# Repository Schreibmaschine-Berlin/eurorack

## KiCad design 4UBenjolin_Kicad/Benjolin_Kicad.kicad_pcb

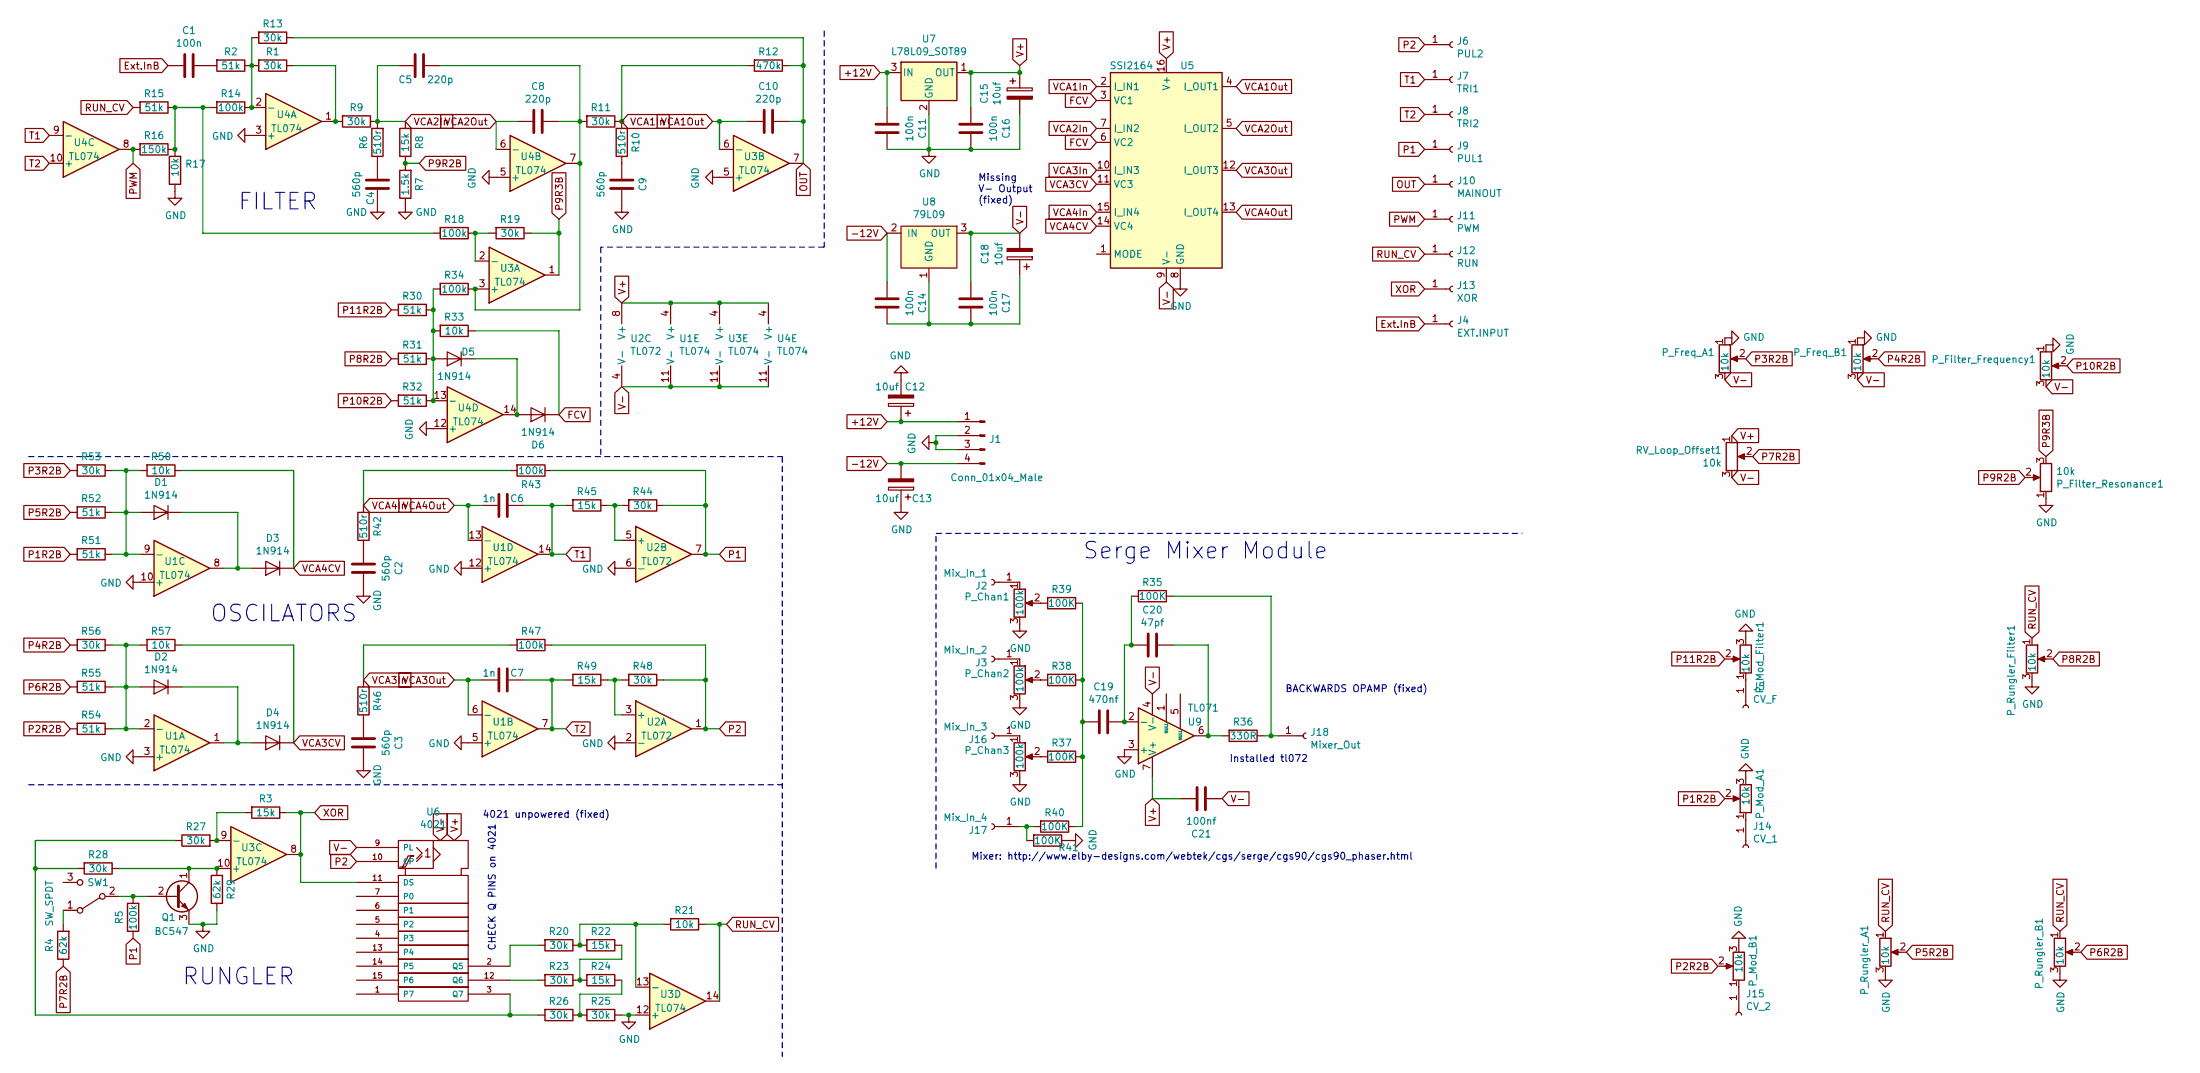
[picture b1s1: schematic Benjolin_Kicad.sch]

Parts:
C1, C11, C14, C16, C17: 100n; C_Disc_D8.0mm_W2.5mm_P5.00mm
C2, C3, C4, C9: 560p; C_Disc_D8.0mm_W2.5mm_P5.00mm
C5, C8, C10: 220p; C_Disc_D8.0mm_W2.5mm_P5.00mm
C6, C7: 1n; C_Disc_D8.0mm_W2.5mm_P5.00mm
C12, C13, C15, C18: 10uf; CP_Radial_D5.0mm_P2.50mm
C19: 470nf; C_Disc_D8.0mm_W2.5mm_P5.00mm
C20: 47pf; C_Disc_D8.0mm_W2.5mm_P5.00mm
C21: 100nf; C_Disc_D8.0mm_W2.5mm_P5.00mm
D1, D2, D3, D4, D5, D6: 1N914; D_A-405_P7.62mm_Horizontal
J1: Conn_01x04_Male; PinHeader_1x04_P2.54mm_Vertical
J2: Mix_In_1; Banana_Jack_PCB
J3: Mix_In_2; Banana_Jack_PCB
J4: EXT.INPUT; Banana_Jack_PCB
J5: CV_F; Banana_Jack_PCB
J6: PUL2; Banana_Jack_PCB
J7: TRI1; Banana_Jack_PCB
J8: TRI2; Banana_Jack_PCB
J9: PUL1; Banana_Jack_PCB
J10: MAINOUT; Banana_Jack_PCB
J11: PWM; Banana_Jack_PCB
J12: RUN; Banana_Jack_PCB
J13: XOR; Banana_Jack_PCB
J14: CV_1; Banana_Jack_PCB
J15: CV_2; Banana_Jack_PCB
J16: Mix_In_3; Banana_Jack_PCB
J17: Mix_In_4; Banana_Jack_PCB
J18: Mixer_Out; Banana_Jack_PCB
P_Chan1, P_Chan2, P_Chan3: 100k; Potentiometer_Alps_RK09K_Single_Vertical
P_Filter_Frequency1: 10k; Potentiometer_Alps_RK09K_Single_Vertical
P_Filter_Resonance1: 10k; Potentiometer_Alps_RK09K_Single_Vertical
P_Freq_A1: 10k; Potentiometer_Alps_RK09K_Single_Vertical
P_Freq_B1: 10k; Potentiometer_Alps_RK09K_Single_Vertical
P_Mod_A1: 10k; Potentiometer_Alps_RK09K_Single_Vertical
P_Mod_B1: 10k; Potentiometer_Alps_RK09K_Single_Vertical
P_Mod_Filter1: 10k; Potentiometer_Alps_RK09K_Single_Vertical
P_Rungler_A1: 10k; Potentiometer_Alps_RK09K_Single_Vertical
P_Rungler_B1: 10k; Potentiometer_Alps_RK09K_Single_Vertical
P_Rungler_Filter1: 10k; Potentiometer_Alps_RK09K_Single_Vertical
Q1: BC547; TO-92_Inline
R1, R9, R11, R13, R19, R20, R23, R25, R26, R27, R28, R44, R48, R53, R56: 30k; R_Axial_DIN0204_L3.6mm_D1.6mm_P7.62mm_Horizontal
R2, R15, R30, R31, R32, R51, R52, R54, R55: 51k; R_Axial_DIN0204_L3.6mm_D1.6mm_P7.62mm_Horizontal
R3, R8, R22, R24, R45, R49: 15k; R_Axial_DIN0204_L3.6mm_D1.6mm_P7.62mm_Horizontal
R4, R29: 62k; R_Axial_DIN0204_L3.6mm_D1.6mm_P7.62mm_Horizontal
R5, R14, R18, R34, R43, R47: 100k; R_Axial_DIN0204_L3.6mm_D1.6mm_P7.62mm_Horizontal
R6, R10, R42, R46: 510r; R_Axial_DIN0204_L3.6mm_D1.6mm_P7.62mm_Horizontal
R7: 1.5k; R_Axial_DIN0204_L3.6mm_D1.6mm_P7.62mm_Horizontal
R12: 470k; R_Axial_DIN0204_L3.6mm_D1.6mm_P7.62mm_Horizontal
R16: 150k; R_Axial_DIN0204_L3.6mm_D1.6mm_P7.62mm_Horizontal
R17, R21, R33, R50, R57: 10k; R_Axial_DIN0204_L3.6mm_D1.6mm_P7.62mm_Horizontal
R35, R37, R38, R39, R40, R41: 100K; R_Axial_DIN0204_L3.6mm_D1.6mm_P7.62mm_Horizontal
R36: 330R; R_Axial_DIN0204_L3.6mm_D1.6mm_P7.62mm_Horizontal
RV_Loop_Offset1: 10k; Potentiometer_Alps_RK09K_Single_Vertical
SW1: SW_SPDT; PinSocket_1x03_P2.54mm_Vertical
U1, U3, U4: TL074; DIP-14_W7.62mm_Socket_LongPads
U2: TL072; DIP-8_W7.62mm_Socket_LongPads
U5: SSI2164; DIP-16_W7.62mm_Socket_LongPads
U6: 4021; DIP-16_W7.62mm_Socket_LongPads
U7: L78L09_SOT89; TO-92L_Inline
U8: 79L09; TO-92L_Inline
U9: TL071; DIP-8_W7.62mm_Socket_LongPads

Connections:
+12V: C11.2, C12.1, J1.1, U7.3 (IN)
-12V: C13.2, C14.2, J1.4, U8.2 (IN)
Ext.InB: C1.2, J4.1
FCV: D6.1 (K), R33.1, U5.3 (VC1), U5.6 (VC2)
GND: C2.1, C3.1, C4.1, C9.1, C11.1, C12.2, C13.1, C15.2, C16.1, J1.2, J1.3, P_Chan1.3, P_Chan2.3, P_Chan3.3, P_Filter_Frequency1.1, P_Filter_Resonance1.1, P_Freq_A1.1, P_Freq_B1.1, P_Mod_A1.3, P_Mod_B1.3, P_Mod_Filter1.3, P_Rungler_A1.3, P_Rungler_B1.3, P_Rungler_Filter1.3, Q1.3 (E), R7.1, R17.1, R25.1, R29.1, R41.1, U1.3 (+), U1.5 (+), U1.10 (+), U1.12 (+), U2.2 (-), U2.6 (-), U3.5 (+), U3.12 (+), U4.3 (+), U4.5 (+), U4.12 (+), U5.8 (GND), U7.2 (GND), U9.3 (+)
unnamed: C1.1, R2.2
unnamed: C2.2, R42.1
unnamed: C3.2, R46.1
unnamed: C4.2, R6.1
unnamed: C5.1, C8.1, R11.2, R34.1, U3.3 (+), U4.7
unnamed: C9.2, R10.1
unnamed: C14.1, C17.1, C18.1, U8.1 (GND)
unnamed: C19.1, C20.2, R35.2, U9.2 (-)
unnamed: C19.2, R37.1, R38.1, R39.1, R40.1
unnamed: C20.1, R36.2, U9.6
unnamed: D1.1 (K), D3.2 (A), U1.8
unnamed: D1.2 (A), R50.2, R51.1, R52.1, R53.1, U1.9 (-)
unnamed: D2.1 (K), D4.2 (A), U1.1
unnamed: D2.2 (A), R54.1, R55.1, R56.1, R57.2, U1.2 (-)
unnamed: D5.1 (K), D6.2 (A), U4.14
unnamed: D5.2 (A), R30.1, R31.1, R32.1, R33.2, R34.2, U4.13 (-)
unnamed: J2.1, P_Chan1.1
unnamed: J3.1, P_Chan2.1
unnamed: J5.1, P_Mod_Filter1.1
unnamed: J14.1, P_Mod_A1.1
unnamed: J15.1, P_Mod_B1.1
unnamed: J16.1, P_Chan3.1
unnamed: J17.1, R40.2, R41.2
unnamed: J18.1, R35.1, R36.1
unnamed: P_Chan1.2, R39.2
unnamed: P_Chan2.2, R38.2
unnamed: P_Chan3.2, R37.2
unnamed: Q1.1 (C), R28.1, R29.2, U3.10 (+)
unnamed: Q1.2 (B), R5.2, SW1.2 (B)
unnamed: R1.1, R9.2, U4.1
unnamed: R1.2, R2.1, R13.2, R14.1, U4.2 (-)
unnamed: R4.2, SW1.1 (A)
unnamed: R14.2, R15.1, R16.1, R17.2, R18.2
unnamed: R18.1, R19.2, U3.2 (-)
unnamed: R20.1, R21.2, R22.2, U3.13 (-)
unnamed: R20.2, U6.2 (Q5)
unnamed: R22.1, R23.1, R24.2
unnamed: R23.2, U6.12 (Q6)
unnamed: R24.1, R25.2, R26.1
unnamed: R26.2, R27.1, R28.2, U6.3 (Q7)
unnamed: R3.2, R27.2, U3.9 (-)
unnamed: R44.2, R45.1, U2.5 (+)
unnamed: R48.2, R49.1, U2.3 (+)
OUT: C10.1, J10.1, R12.1, R13.1, U3.7
P1: J9.1, R5.1, R43.1, R44.1, U2.7
P1R2B: P_Mod_A1.2, R51.2
P2: J6.1, R47.1, R48.1, U2.1, U6.10 (CP)
P2R2B: P_Mod_B1.2, R54.2
P3R2B: P_Freq_A1.2, R53.2
P4R2B: P_Freq_B1.2, R56.2
P5R2B: P_Rungler_A1.2, R52.2
P6R2B: P_Rungler_B1.2, R55.2
P7R2B: R4.1, RV_Loop_Offset1.2
P8R2B: P_Rungler_Filter1.2, R31.2
P9R2B: P_Filter_Resonance1.2, R7.2, R8.1
P9R3B: P_Filter_Resonance1.3, R19.1, U3.1
P10R2B: P_Filter_Frequency1.2, R32.2
P11R2B: P_Mod_Filter1.2, R30.2
PWM: J11.1, R16.2, U4.8
RUN_CV: J12.1, P_Rungler_A1.1, P_Rungler_B1.1, P_Rungler_Filter1.1, R15.2, R21.1, U3.14
T1: C6.1, J7.1, R45.2, U1.14, U4.9 (-)
T2: C7.1, J8.1, R49.2, U1.7, U4.10 (+)
V+: C15.1, C16.2, C21.1, RV_Loop_Offset1.1, U1.4 (V+), U2.8 (V+), U3.4 (V+), U4.4 (V+), U5.16 (V+), U6.16 (Vdd), U7.1 (OUT), U9.7 (V+)
V-: C17.2, C18.2, C21.2, P_Filter_Frequency1.3, P_Freq_A1.3, P_Freq_B1.3, RV_Loop_Offset1.3, U1.11 (V-), U2.4 (V-), U3.11 (V-), U4.11 (V-), U5.9 (V-), U6.8 (Vss), U6.9 (PL), U8.3 (OUT), U9.4 (V-)
VCA1In: R10.2, R11.1, R12.2, U5.2 (I_IN1)
VCA1Out: C10.2, U3.6 (-), U5.4 (I_OUT1)
VCA2In: C5.2, R6.2, R8.2, R9.1, U5.7 (I_IN2)
VCA2Out: C8.2, U4.6 (-), U5.5 (I_OUT2)
VCA3CV: D4.1 (K), R57.1, U5.11 (VC3)
VCA3In: R46.2, R47.2, U5.10 (I_IN3)
VCA3Out: C7.2, U1.6 (-), U5.12 (I_OUT3)
VCA4CV: D3.1 (K), R50.1, U5.14 (VC4)
VCA4In: R42.2, R43.2, U5.15 (I_IN4)
VCA4Out: C6.2, U1.13 (-), U5.13 (I_OUT4)
XOR: J13.1, R3.1, U3.8, U6.11 (DS)

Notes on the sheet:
FILTER
RUNGLER
OSCILATORS
Mixer: http://www.elby-designs.com/webtek/cgs/serge/cgs90/cgs90_phaser.html
Serge Mixer Module
BACKWARDS OPAMP (fixed)
CHECK Q PINS on 4021
Missing V- Output (fixed)
Installed tl072
4021 unpowered (fixed)

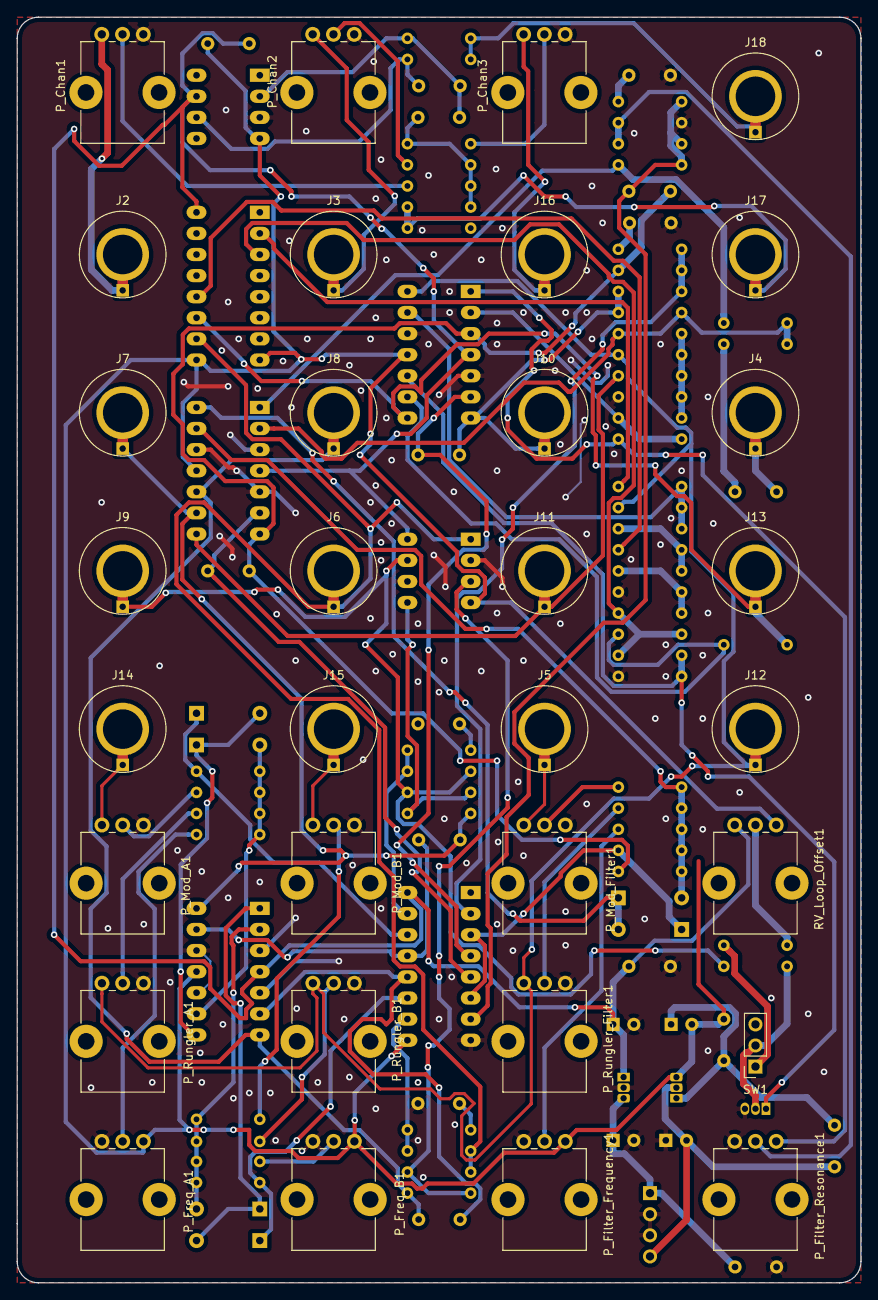
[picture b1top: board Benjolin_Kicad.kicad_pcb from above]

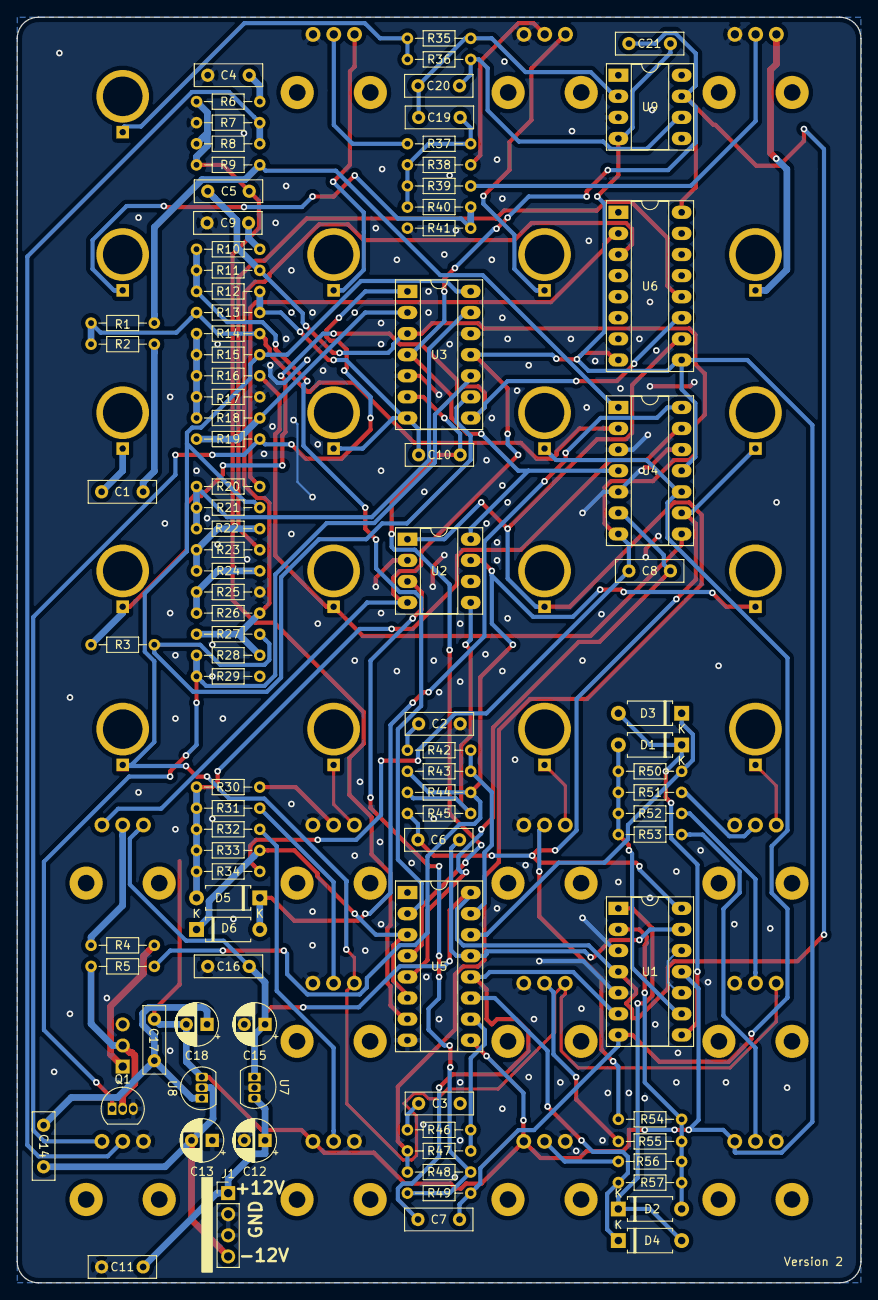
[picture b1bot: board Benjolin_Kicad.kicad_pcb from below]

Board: 2 copper layers, 101.6 x 152.4 mm, 127 parts (95 on the bottom side), 80 nets.

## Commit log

2019-01-28 created Most Logic Module kicad
2019-01-30 Started voltage adder project
2019-01-31 Added voltage division, I/O, logic and mixer to the Semitone Voltage Adder
2019-02-05 added buffered mult stage
2019-03-17 Added the test file
2019-07-09 Added repo for 4U benjolin version
2019-07-10 Added footprint for Banana Panel Cutout and built up a generic 4u Front Panel
2019-07-11 Added footprint for banana panel and started 4U version of benjolin
2019-07-12 Added footprints for banana PCB and made pcb size
2019-07-14 Added footprints and symbols. added a mixer to the panel
2019-07-15 Working on board layout
2019-07-15 ready for traces
2019-07-17 traces complete
2019-07-17 fixed banana panel cutout, designed front panel for Benjolin, Fixed pot orientation
2019-07-18 worked on front panel
2019-07-24 Final? just need to seperate boards
2019-07-24 pots are off center still and need to connect one of the ground pins
2019-07-24 made separate panel
2019-08-06 Built Gerbers
2019-08-21 Changed to circular holes on the front panel
2019-08-21 Circular panel holes with gerbers
2019-09-08 Some minor layout stuff
2019-09-08 All bugs fixed. -v rail, flipped pots, power to 4021, tl071 opamp flipped
2019-09-08 Renumbered the resistors. V2 built and sent to jlcpcb
2020-09-14 Init kicad cad project named 1U Atari Punk
2020-09-14 Preliminary work
2020-09-14 Cleaned up the schematic
    I copied the components and made a cleaned up version for comparison. Make sure to delete the original before continuing
2020-09-15 Fixed Ground on pin 7
2020-09-16 Started the big logic module
2020-09-17 I accidentally solved the Even/Odd problem
2020-09-18 I think I solved the Exact count problem
    It is the same as the input sorting problem, could be combined?
2020-09-20 Added Exactly and <> functions
2021-01-16 Added some new ideas
    Problem with 3 voice synth library
2021-03-06 Fixed gnd point and started redraw of schematic
